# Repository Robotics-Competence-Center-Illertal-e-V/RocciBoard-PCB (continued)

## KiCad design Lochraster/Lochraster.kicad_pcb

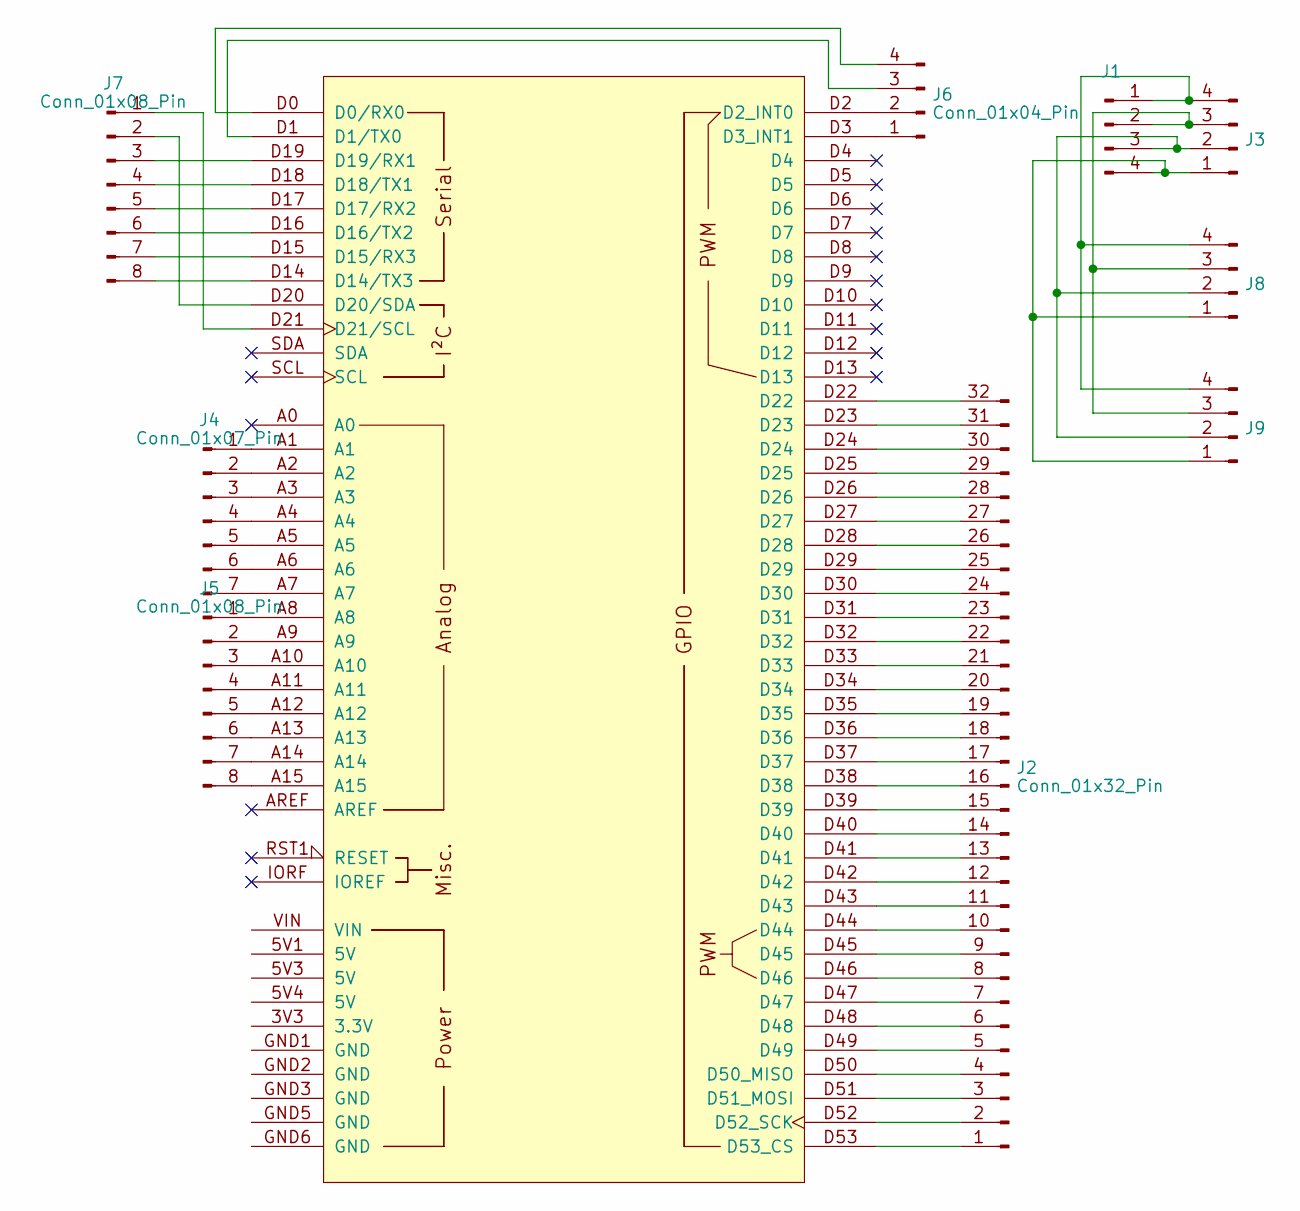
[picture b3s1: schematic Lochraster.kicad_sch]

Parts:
J1, J3, J8, J9: Conn_01x04_Pin; PinHeader_1x04_P2.54mm_Vertical
J2: Conn_01x32_Pin; PinSocket_2x16_P2.54mm_Vertical
J4: Conn_01x07_Pin; PinSocket_1x07_P2.54mm_Vertical
J5, J7: Conn_01x08_Pin; PinSocket_1x08_P2.54mm_Vertical
J6: Conn_01x04_Pin; PinSocket_1x04_P2.54mm_Vertical
XA1: Arduino_Mega2560_Shield; Arduino_Mega2560_custom_Shield

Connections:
unnamed: J1.1, J3.4, J8.4, J9.4
unnamed: J1.2, J3.3, J8.3, J9.3
unnamed: J1.3, J3.2, J8.2, J9.2
unnamed: J1.4, J3.1, J8.1, J9.1
unnamed: J2.1, XA1.D53 (D53_CS)
unnamed: J2.2, XA1.D52 (D52_SCK)
unnamed: J2.3, XA1.D51 (D51_MOSI)
unnamed: J2.4, XA1.D50 (D50_MISO)
unnamed: J2.5, XA1.D49
unnamed: J2.6, XA1.D48
unnamed: J2.7, XA1.D47
unnamed: J2.8, XA1.D46
unnamed: J2.9, XA1.D45
unnamed: J2.10, XA1.D44
unnamed: J2.11, XA1.D43
unnamed: J2.12, XA1.D42
unnamed: J2.13, XA1.D41
unnamed: J2.14, XA1.D40
unnamed: J2.15, XA1.D39
unnamed: J2.16, XA1.D38
unnamed: J2.17, XA1.D37
unnamed: J2.18, XA1.D36
unnamed: J2.19, XA1.D35
unnamed: J2.20, XA1.D34
unnamed: J2.21, XA1.D33
unnamed: J2.22, XA1.D32
unnamed: J2.23, XA1.D31
unnamed: J2.24, XA1.D30
unnamed: J2.25, XA1.D29
unnamed: J2.26, XA1.D28
unnamed: J2.27, XA1.D27
unnamed: J2.28, XA1.D26
unnamed: J2.29, XA1.D25
unnamed: J2.30, XA1.D24
unnamed: J2.31, XA1.D23
unnamed: J2.32, XA1.D22
unnamed: J4.1, XA1.A1
unnamed: J4.2, XA1.A2
unnamed: J4.3, XA1.A3
unnamed: J4.4, XA1.A4
unnamed: J4.5, XA1.A5
unnamed: J4.6, XA1.A6
unnamed: J4.7, XA1.A7
unnamed: J5.1, XA1.A8
unnamed: J5.2, XA1.A9
unnamed: J5.3, XA1.A10
unnamed: J5.4, XA1.A11
unnamed: J5.5, XA1.A12
unnamed: J5.6, XA1.A13
unnamed: J5.7, XA1.A14
unnamed: J5.8, XA1.A15
unnamed: J6.1, XA1.D3 (D3_INT1)
unnamed: J6.2, XA1.D2 (D2_INT0)
unnamed: J6.3, XA1.D1 (D1/TX0)
unnamed: J6.4, XA1.D0 (D0/RX0)
unnamed: J7.1, XA1.D21 (D21/SCL)
unnamed: J7.2, XA1.D20 (D20/SDA)
unnamed: J7.3, XA1.D19 (D19/RX1)
unnamed: J7.4, XA1.D18 (D18/TX1)
unnamed: J7.5, XA1.D17 (D17/RX2)
unnamed: J7.6, XA1.D16 (D16/TX2)
unnamed: J7.7, XA1.D15 (D15/RX3)
unnamed: J7.8, XA1.D14 (D14/TX3)

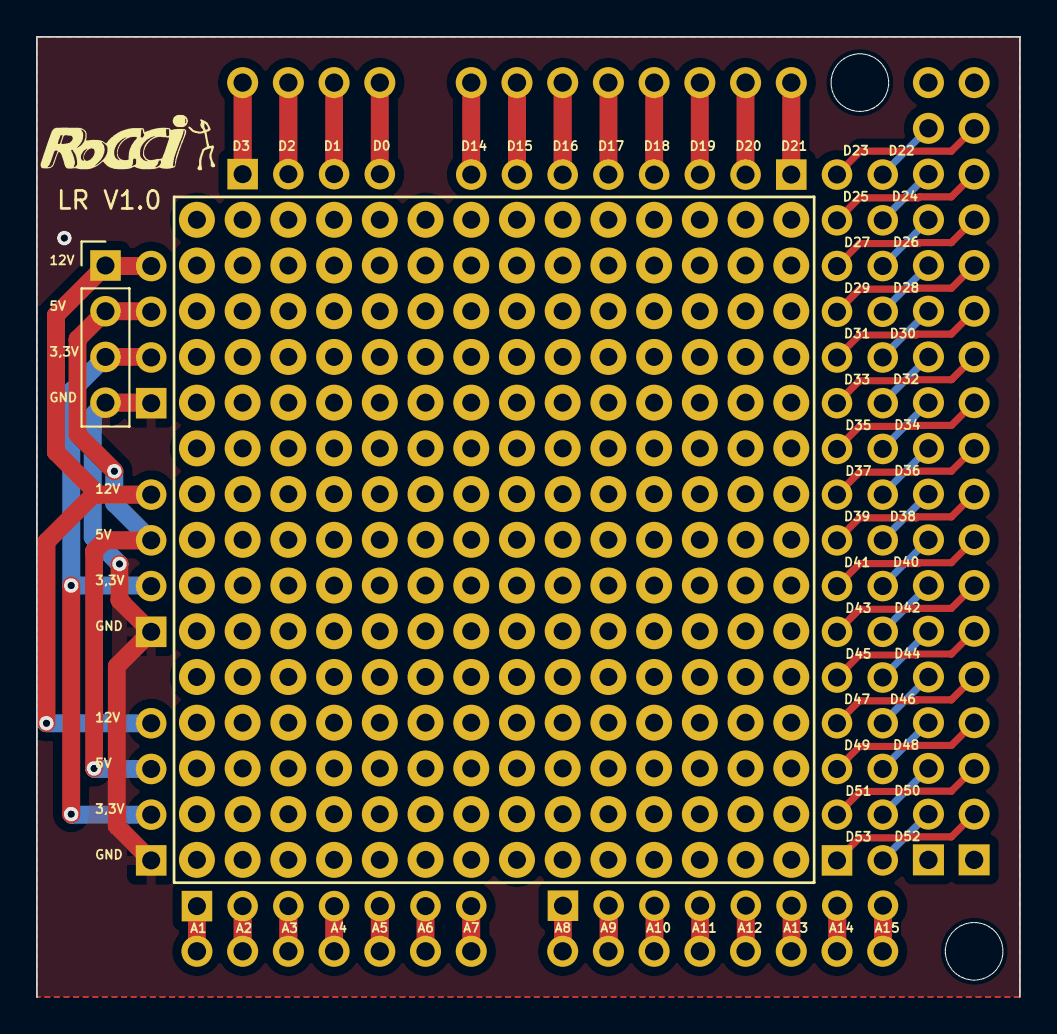
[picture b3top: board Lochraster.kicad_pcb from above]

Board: 2 copper layers, 54.6 x 53.3 mm, 10 parts (0 on the bottom side), 63 nets.

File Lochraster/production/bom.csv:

Designator,Footprint,Quantity,Value,LCSC Part #
"J1, J3, J8, J9",PinHeader_1x04_P2.54mm_Vertical,4,Conn_01x04_Pin,
J2,PinSocket_2x16_P2.54mm_Vertical,1,Conn_01x32_Pin,
J4,PinSocket_1x07_P2.54mm_Vertical,1,Conn_01x07_Pin,
"J5, J7",PinSocket_1x08_P2.54mm_Vertical,2,Conn_01x08_Pin,
J6,PinSocket_1x04_P2.54mm_Vertical,1,Conn_01x04_Pin,
XA1,Arduino_Mega2560_custom_Shield,1,Arduino_Mega2560_Shield,

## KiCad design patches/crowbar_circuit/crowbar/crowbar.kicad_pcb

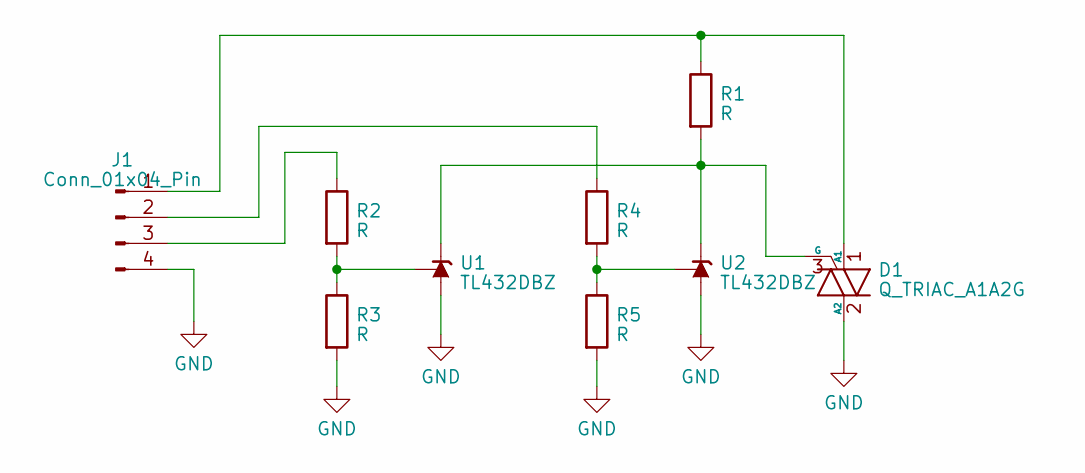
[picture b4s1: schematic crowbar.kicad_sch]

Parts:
D1: Q_TRIAC_A1A2G; TO-252-2
J1: Conn_01x04_Pin; PinHeader_1x04_P2.54mm_Vertical
R1, R2, R3, R4, R5: R; R_0805_2012Metric_Pad1.20x1.40mm_HandSolder
U1, U2: TL432DBZ; SOT-23

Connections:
GND: D1.2 (A2), J1.4, R3.2, R5.2, U1.3 (A), U2.3 (A)
unnamed: D1.1 (A1), J1.1, R1.1
unnamed: D1.3 (G), R1.2, U1.2 (K), U2.2 (K)
unnamed: J1.2, R4.1
unnamed: J1.3, R2.1
unnamed: R2.2, R3.1, U1.1 (REF)
unnamed: R4.2, R5.1, U2.1 (REF)

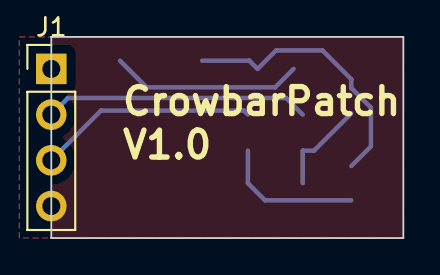
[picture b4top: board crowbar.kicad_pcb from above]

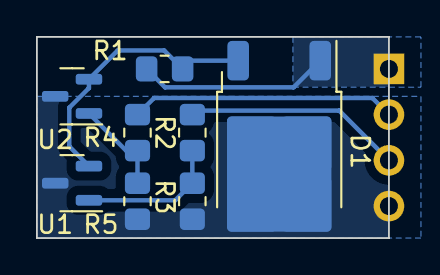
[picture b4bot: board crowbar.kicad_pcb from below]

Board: 2 copper layers, 19.6 x 11.2 mm, 9 parts (8 on the bottom side), 7 nets.

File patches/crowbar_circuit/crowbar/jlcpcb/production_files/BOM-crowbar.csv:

Comment,Designator,Footprint,LCSC
TL432DBZ,U2,SOT-23,
TL432DBZ,U1,SOT-23,
R,R5,R_0805_2012Metric_Pad1.20x1.40mm_HandSolder,
R,R4,R_0805_2012Metric_Pad1.20x1.40mm_HandSolder,
R,R3,R_0805_2012Metric_Pad1.20x1.40mm_HandSolder,
R,R2,R_0805_2012Metric_Pad1.20x1.40mm_HandSolder,
R,R1,R_0805_2012Metric_Pad1.20x1.40mm_HandSolder,
Conn_01x04_Pin,J1,PinHeader_1x04_P2.54mm_Vertical,
Q_TRIAC_A1A2G,D1,TO-252-2,

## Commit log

2023-06-23 first draft of schematic almost complete
2023-06-23 added pdf
2023-06-23 add some changes
2023-06-23 fixed issue #1 and some more things
2023-06-23 added zener diode
2023-06-24 changed pwm pins, added footprints, started JLPCB component selection
2023-06-25 change linear regulator to lm317 (jlc basic part)
2023-06-26 added changes from #2
2023-06-27 finished JLCPCB selection and fixed isse #3
2023-06-29 added more TODOs
2023-07-01 first placment finished. Needs some adjustment
2023-07-05 first finished routing. Needs some cleanup
2023-07-13 finsihed routing again
2023-07-14 finished silcreen and 3d files
2023-07-18 layout ready for review
2023-07-18 added some documenation update
2023-07-19 changed i2c order
2023-07-19 aligned components
2023-07-19 renamed project file to RocciBoard
2023-07-19 finished #4 TODO list
2023-07-19 cleanup
2023-07-26 lochraster ist fertig
2023-07-26 remove unused pads
2023-07-27 final version V1.0
2023-07-29 V1.0 finished
2023-07-30 added layout as pdf
2023-09-29 patch issue #9 add crowbar circuit piggyback pcb
2023-09-29 fixed #6 1k LCSL part number was wrong
2023-09-29 fix #8 prevent backcurrent from Arduino USB
2023-09-29 fix #5 Error LED Q2 Source<->Drain vertauscht
2023-09-29 fix #7 all status LEDs are too bright
2023-09-29 fix #9 OVP 12V<->5V short circuit protection
2023-09-30 V 1.1
2024-09-01 fix #13 #12 #11 #10
2024-09-01 cleanup production files
2025-02-28 rework Lochraster for larger pads
2025-07-15 added 2S lipo support to the schematic
2025-07-15 add xt60 and spereate i2c pwr and data jumper
2025-07-24 more progress with nxt shield
2025-09-29 update rocci board to have XT60 and more jumper
2025-09-29 first version of NXT shield with nxt sensors
2025-11-08 nxt shield first prototype production
2025-11-08 update rocciboard with thermal release
2026-01-09 Version 1.2 finished
